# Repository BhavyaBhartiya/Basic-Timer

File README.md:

# Basic-Timer

This is a timer made using one CD4060 IC and two NE555 ICs with values of 1, 2, 4, 8, 16, 32 and 64 mins and with different ringtones that can be changed by rotating a button.

## Schematic

## PCB

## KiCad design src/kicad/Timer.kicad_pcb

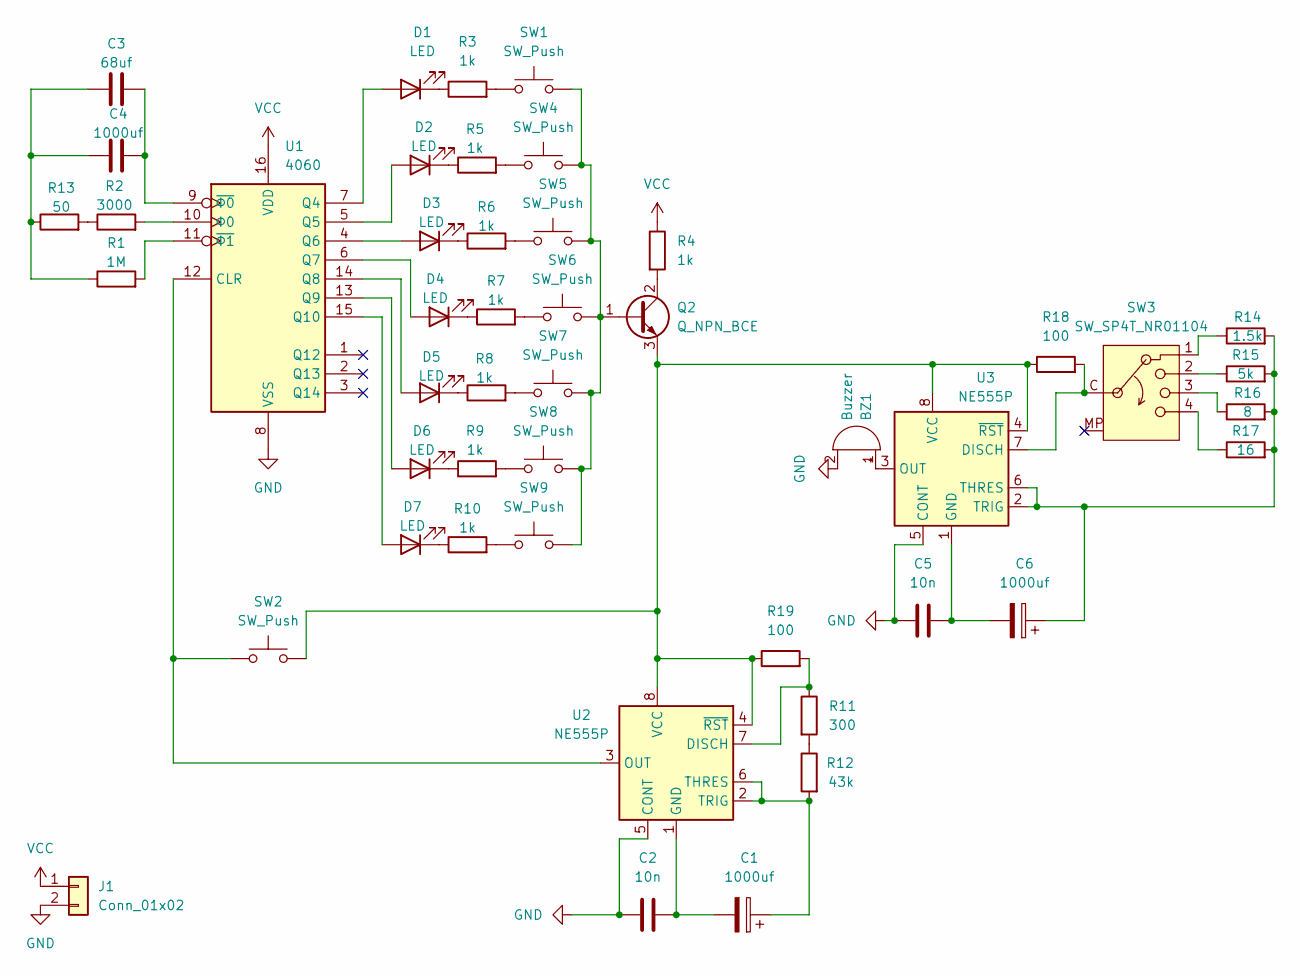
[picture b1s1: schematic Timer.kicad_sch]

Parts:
BZ1: Buzzer; Buzzer_12x9.5RM7.6
C1, C4, C6: 1000uf; C_Disc_D5.0mm_W2.5mm_P5.00mm
C2, C5: 10n; C_Disc_D5.0mm_W2.5mm_P5.00mm
C3: 68uf; C_Disc_D5.0mm_W2.5mm_P5.00mm
D1, D2, D3, D4, D5, D6, D7: LED; LED_D5.0mm
J1: Conn_01x02; PinHeader_1x02_P2.54mm_Vertical
Q2: Q_NPN_BCE; TO-92L_Inline_Wide
R1: 1M; R_Axial_DIN0204_L3.6mm_D1.6mm_P7.62mm_Horizontal
R2: 3000; R_Axial_DIN0204_L3.6mm_D1.6mm_P7.62mm_Horizontal
R3, R4, R5, R6, R7, R8, R9, R10: 1k; R_Axial_DIN0204_L3.6mm_D1.6mm_P7.62mm_Horizontal
R11: 300; R_Axial_DIN0204_L3.6mm_D1.6mm_P7.62mm_Horizontal
R12: 43k; R_Axial_DIN0204_L3.6mm_D1.6mm_P7.62mm_Horizontal
R13: 50; R_Axial_DIN0204_L3.6mm_D1.6mm_P7.62mm_Horizontal
R14: 1.5k; R_Axial_DIN0204_L3.6mm_D1.6mm_P7.62mm_Horizontal
R15: 5k; R_Axial_DIN0204_L3.6mm_D1.6mm_P7.62mm_Horizontal
R16: 8; R_Axial_DIN0204_L3.6mm_D1.6mm_P7.62mm_Horizontal
R17: 16; R_Axial_DIN0204_L3.6mm_D1.6mm_P7.62mm_Horizontal
R18, R19: 100; R_Axial_DIN0204_L3.6mm_D1.6mm_P7.62mm_Horizontal
SW1, SW2, SW4, SW5, SW6, SW7, SW8, SW9: SW_Push; SW_PUSH_6mm
SW3: SW_SP4T_NR01104; SW_NKK_NR01
U1: 4060; DIP-16_W7.62mm
U2, U3: NE555P; DIP-8_W7.62mm

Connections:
GND: BZ1.2 (-), C2.2, C5.2, J1.2, U1.8 (VSS), U2.5 (CONT), U3.5 (CONT)
unnamed: BZ1.1 (+), U3.3 (OUT)
unnamed: C3.1, C4.1, R1.1, R13.1
unnamed: D1.2 (A), U1.7 (Q4)
unnamed: D1.1 (K), R3.1
unnamed: D2.2 (A), U1.5 (Q5)
unnamed: D2.1 (K), R5.1
unnamed: D3.2 (A), U1.4 (Q6)
unnamed: D3.1 (K), R6.1
unnamed: D4.2 (A), U1.6 (Q7)
unnamed: D4.1 (K), R7.1
unnamed: D5.2 (A), U1.14 (Q8)
unnamed: D5.1 (K), R8.1
unnamed: D6.2 (A), U1.13 (Q9)
unnamed: D6.1 (K), R9.1
unnamed: D7.2 (A), U1.15 (Q10)
unnamed: D7.1 (K), R10.1
unnamed: Q2.1 (B), SW1.2, SW4.2, SW5.2, SW6.2, SW7.2, SW8.2, SW9.2
unnamed: Q2.2 (C), R4.2
unnamed: Q2.3 (E), R18.1, R19.1, SW2.2, U2.4 (~RST), U2.8 (VCC), U3.4 (~RST), U3.8 (VCC)
unnamed: R3.2, SW1.1
unnamed: R5.2, SW4.1
unnamed: R6.2, SW5.1
unnamed: R7.2, SW6.1
unnamed: R8.2, SW7.1
unnamed: R9.2, SW8.1
unnamed: R10.2, SW9.1
unnamed: R11.2, R12.1
unnamed: R2.1, R13.2
unnamed: R14.1, SW3.1
unnamed: R15.1, SW3.2
unnamed: R16.1, SW3.3
unnamed: R17.1, SW3.4
unnamed: R18.2, SW3.C (Common), U3.7 (DISCH)
unnamed: SW2.1, U1.12 (CLR), U2.3 (OUT)
unnamed: C3.2, C4.2, U1.9 (~Φ0)
unnamed: R1.2, U1.11 (~Φ1)
unnamed: R2.2, U1.10 (Φ0)
unnamed: R11.1, R19.2, U2.7 (DISCH)
unnamed: C1.2, C2.1, U2.1 (GND)
unnamed: C1.1, R12.2, U2.2 (TRIG), U2.6 (THRES)
unnamed: C5.1, C6.2, U3.1 (GND)
unnamed: C6.1, R14.2, R15.2, R16.2, R17.2, U3.2 (TRIG), U3.6 (THRES)
VCC: J1.1, R4.1, U1.16 (VDD)

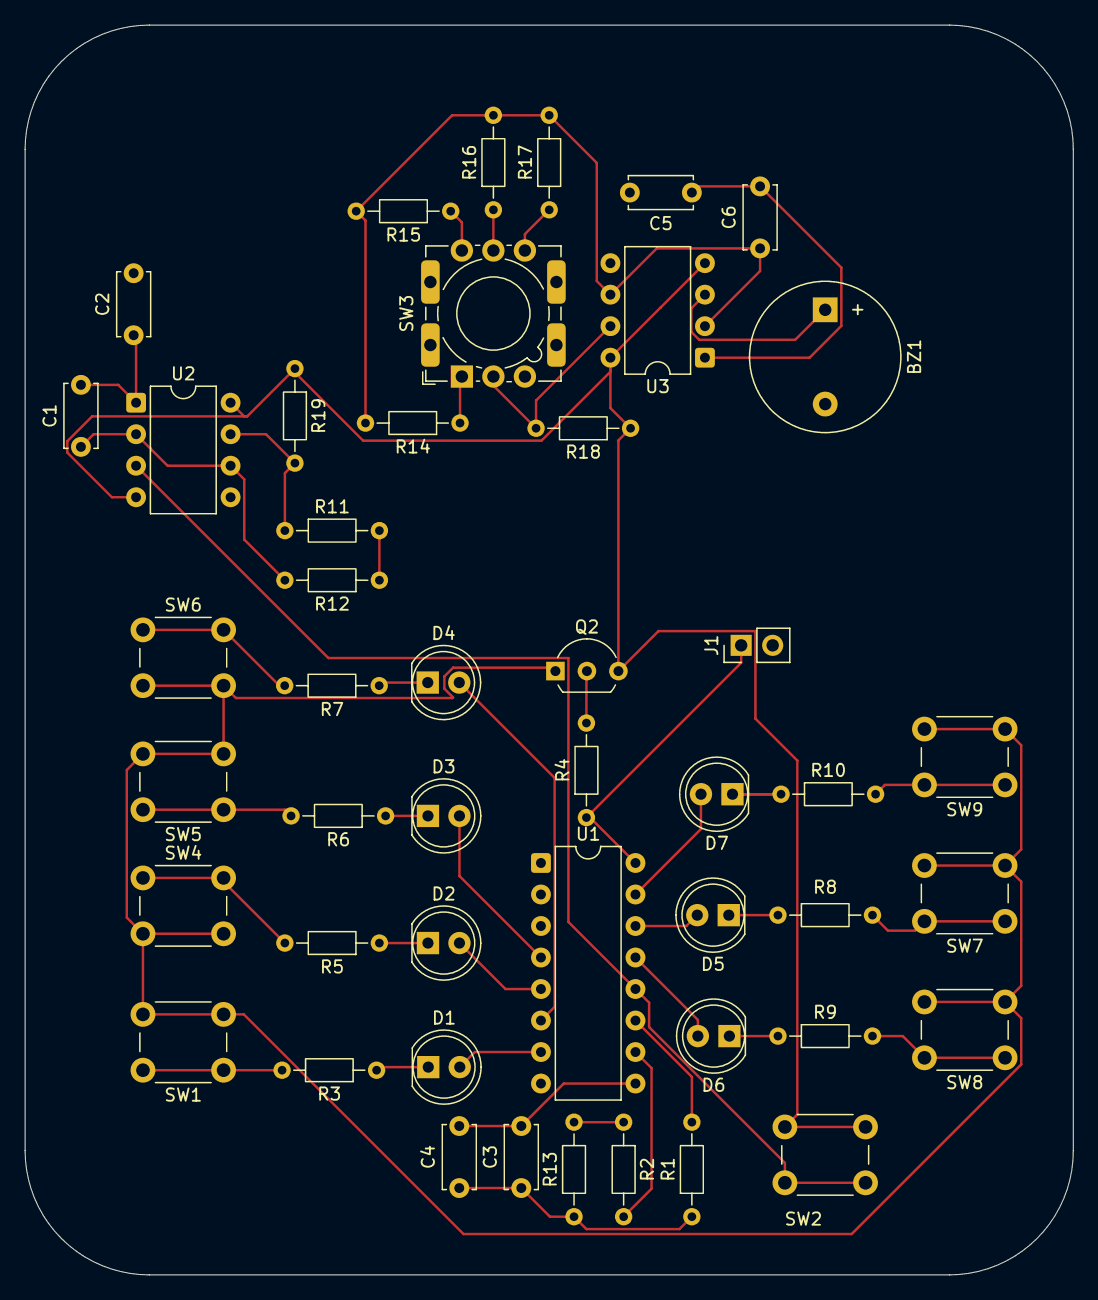
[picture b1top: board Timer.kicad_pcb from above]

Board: 2 copper layers, 84.5 x 100.8 mm, 47 parts (0 on the bottom side), 44 nets.

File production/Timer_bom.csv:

Designator,Footprint,Quantity,Value,LCSC Part #
BZ1,Buzzer_12x9.5RM7.6,1,Buzzer,
"C1, C4, C6",C_Disc_D5.0mm_W2.5mm_P5.00mm,3,1000uf,
"C2, C5",C_Disc_D5.0mm_W2.5mm_P5.00mm,2,10n,
C3,C_Disc_D5.0mm_W2.5mm_P5.00mm,1,68uf,
"D1, D2, D3, D4, D5, D6, D7",LED_D5.0mm,7,LED,
J1,PinHeader_1x02_P2.54mm_Vertical,1,Conn_01x02,
Q2,TO-92L_Inline_Wide,1,Q_NPN_BCE,
R1,R_Axial_DIN0204_L3.6mm_D1.6mm_P7.62mm_Horizontal,1,1M,
"R10, R3, R4, R5, R6, R7, R8, R9",R_Axial_DIN0204_L3.6mm_D1.6mm_P7.62mm_Horizontal,8,1k,
R11,R_Axial_DIN0204_L3.6mm_D1.6mm_P7.62mm_Horizontal,1,300,
R12,R_Axial_DIN0204_L3.6mm_D1.6mm_P7.62mm_Horizontal,1,43k,
R13,R_Axial_DIN0204_L3.6mm_D1.6mm_P7.62mm_Horizontal,1,50,
R14,R_Axial_DIN0204_L3.6mm_D1.6mm_P7.62mm_Horizontal,1,1.5k,
R15,R_Axial_DIN0204_L3.6mm_D1.6mm_P7.62mm_Horizontal,1,5k,
R16,R_Axial_DIN0204_L3.6mm_D1.6mm_P7.62mm_Horizontal,1,8,
R17,R_Axial_DIN0204_L3.6mm_D1.6mm_P7.62mm_Horizontal,1,16,
"R18, R19",R_Axial_DIN0204_L3.6mm_D1.6mm_P7.62mm_Horizontal,2,100,
R2,R_Axial_DIN0204_L3.6mm_D1.6mm_P7.62mm_Horizontal,1,3000,
"SW10, SW4, SW5, SW6, SW7, SW8, SW9",SW_PUSH_6mm,7,SW_DIP_x01,
SW2,SW_PUSH_6mm,1,SW_Push,
SW3,SW_NKK_NR01,1,SW_SP4T_NR01104,
U1,DIP-16_W7.62mm,1,4060,
"U2, U3",DIP-8_W7.62mm,2,NE555P,

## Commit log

2026-04-11 Create a
